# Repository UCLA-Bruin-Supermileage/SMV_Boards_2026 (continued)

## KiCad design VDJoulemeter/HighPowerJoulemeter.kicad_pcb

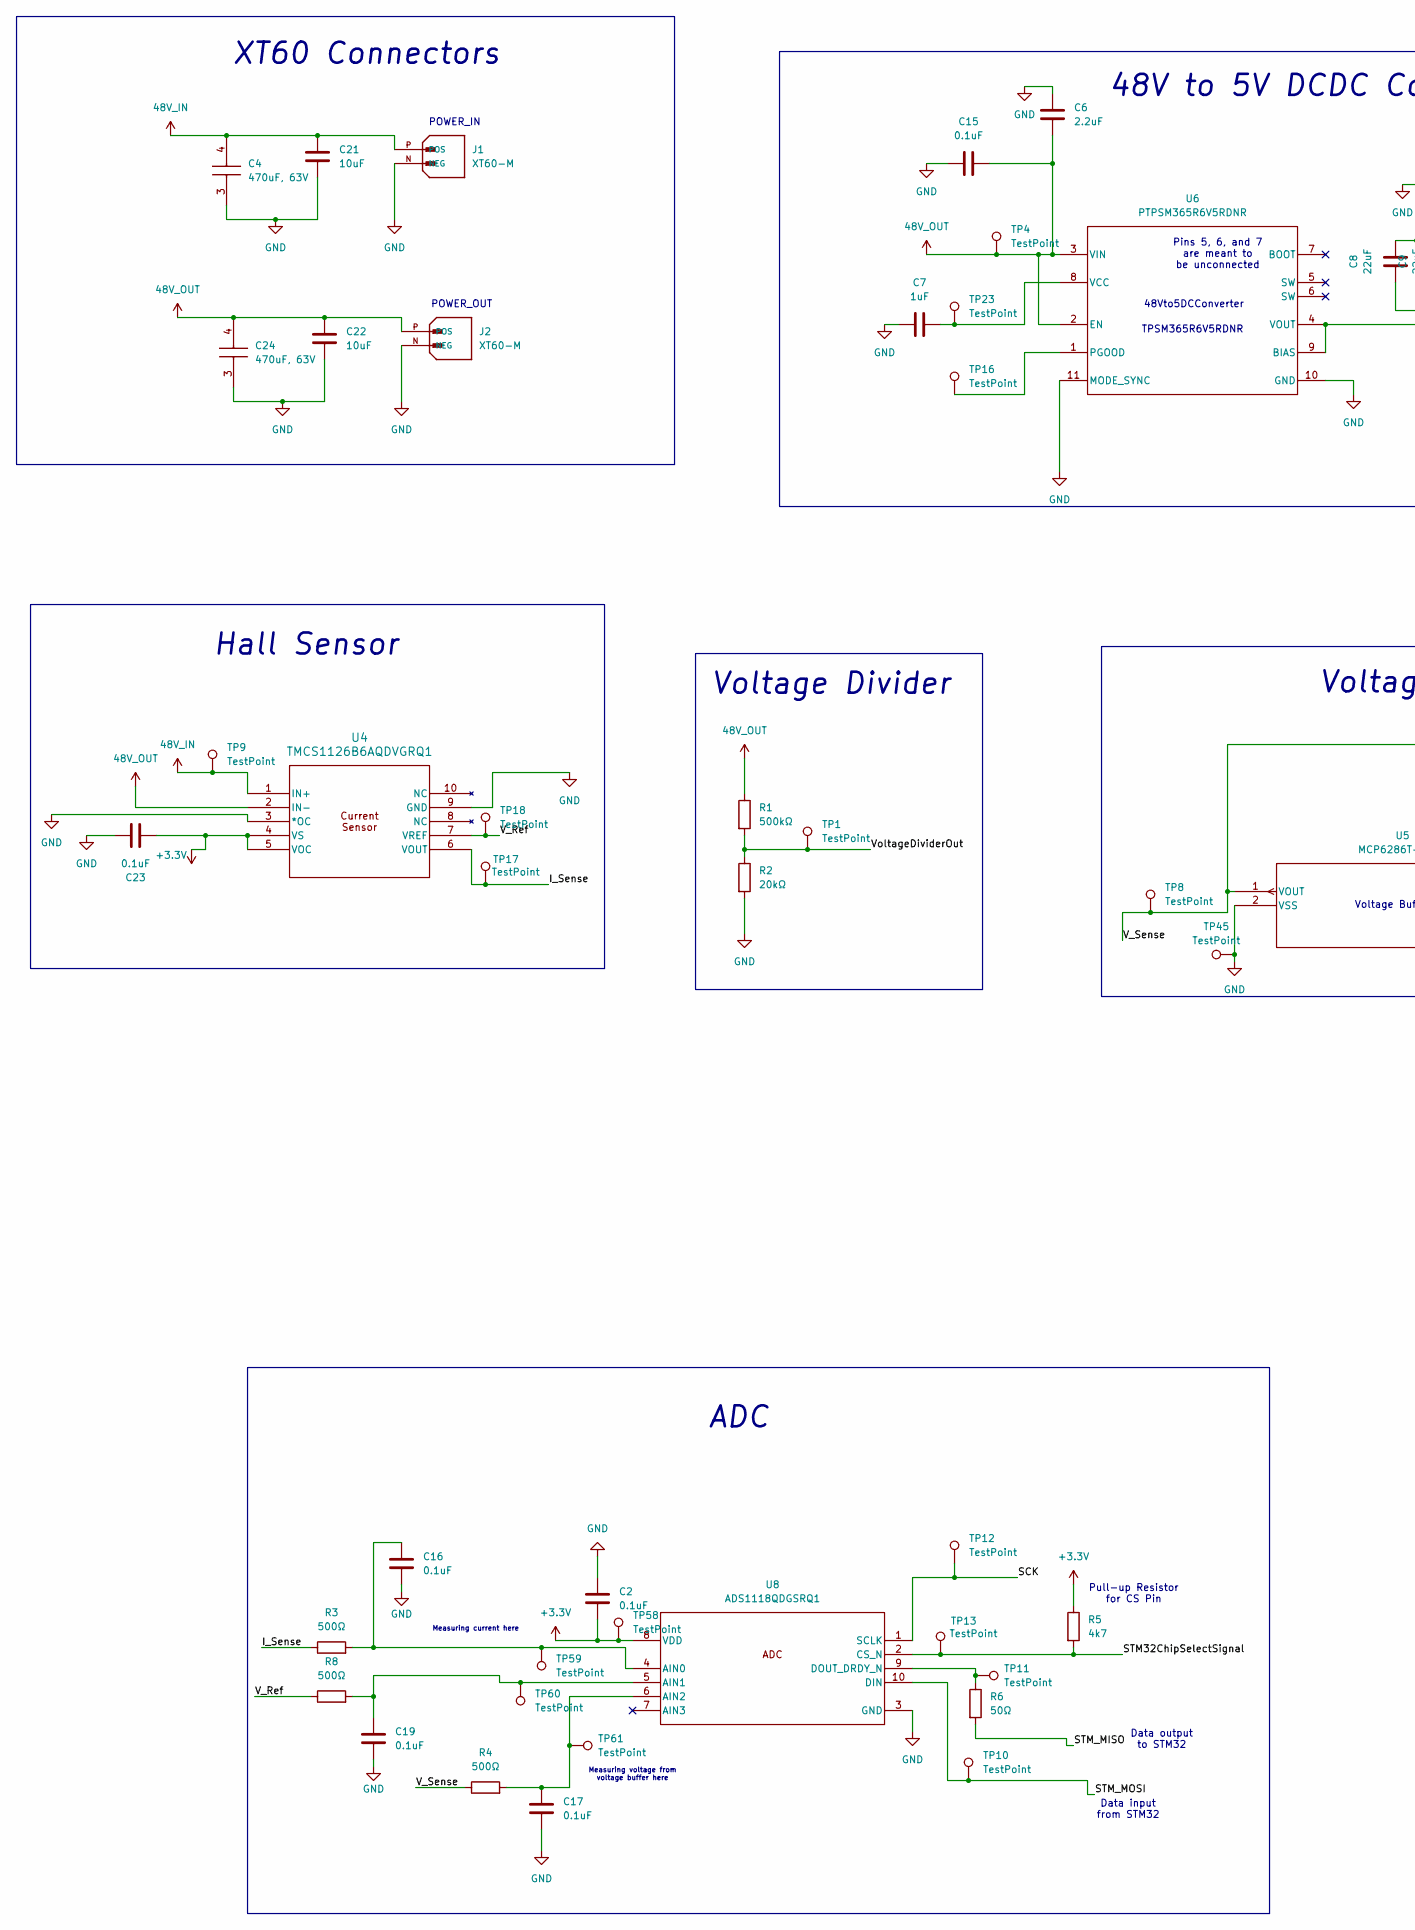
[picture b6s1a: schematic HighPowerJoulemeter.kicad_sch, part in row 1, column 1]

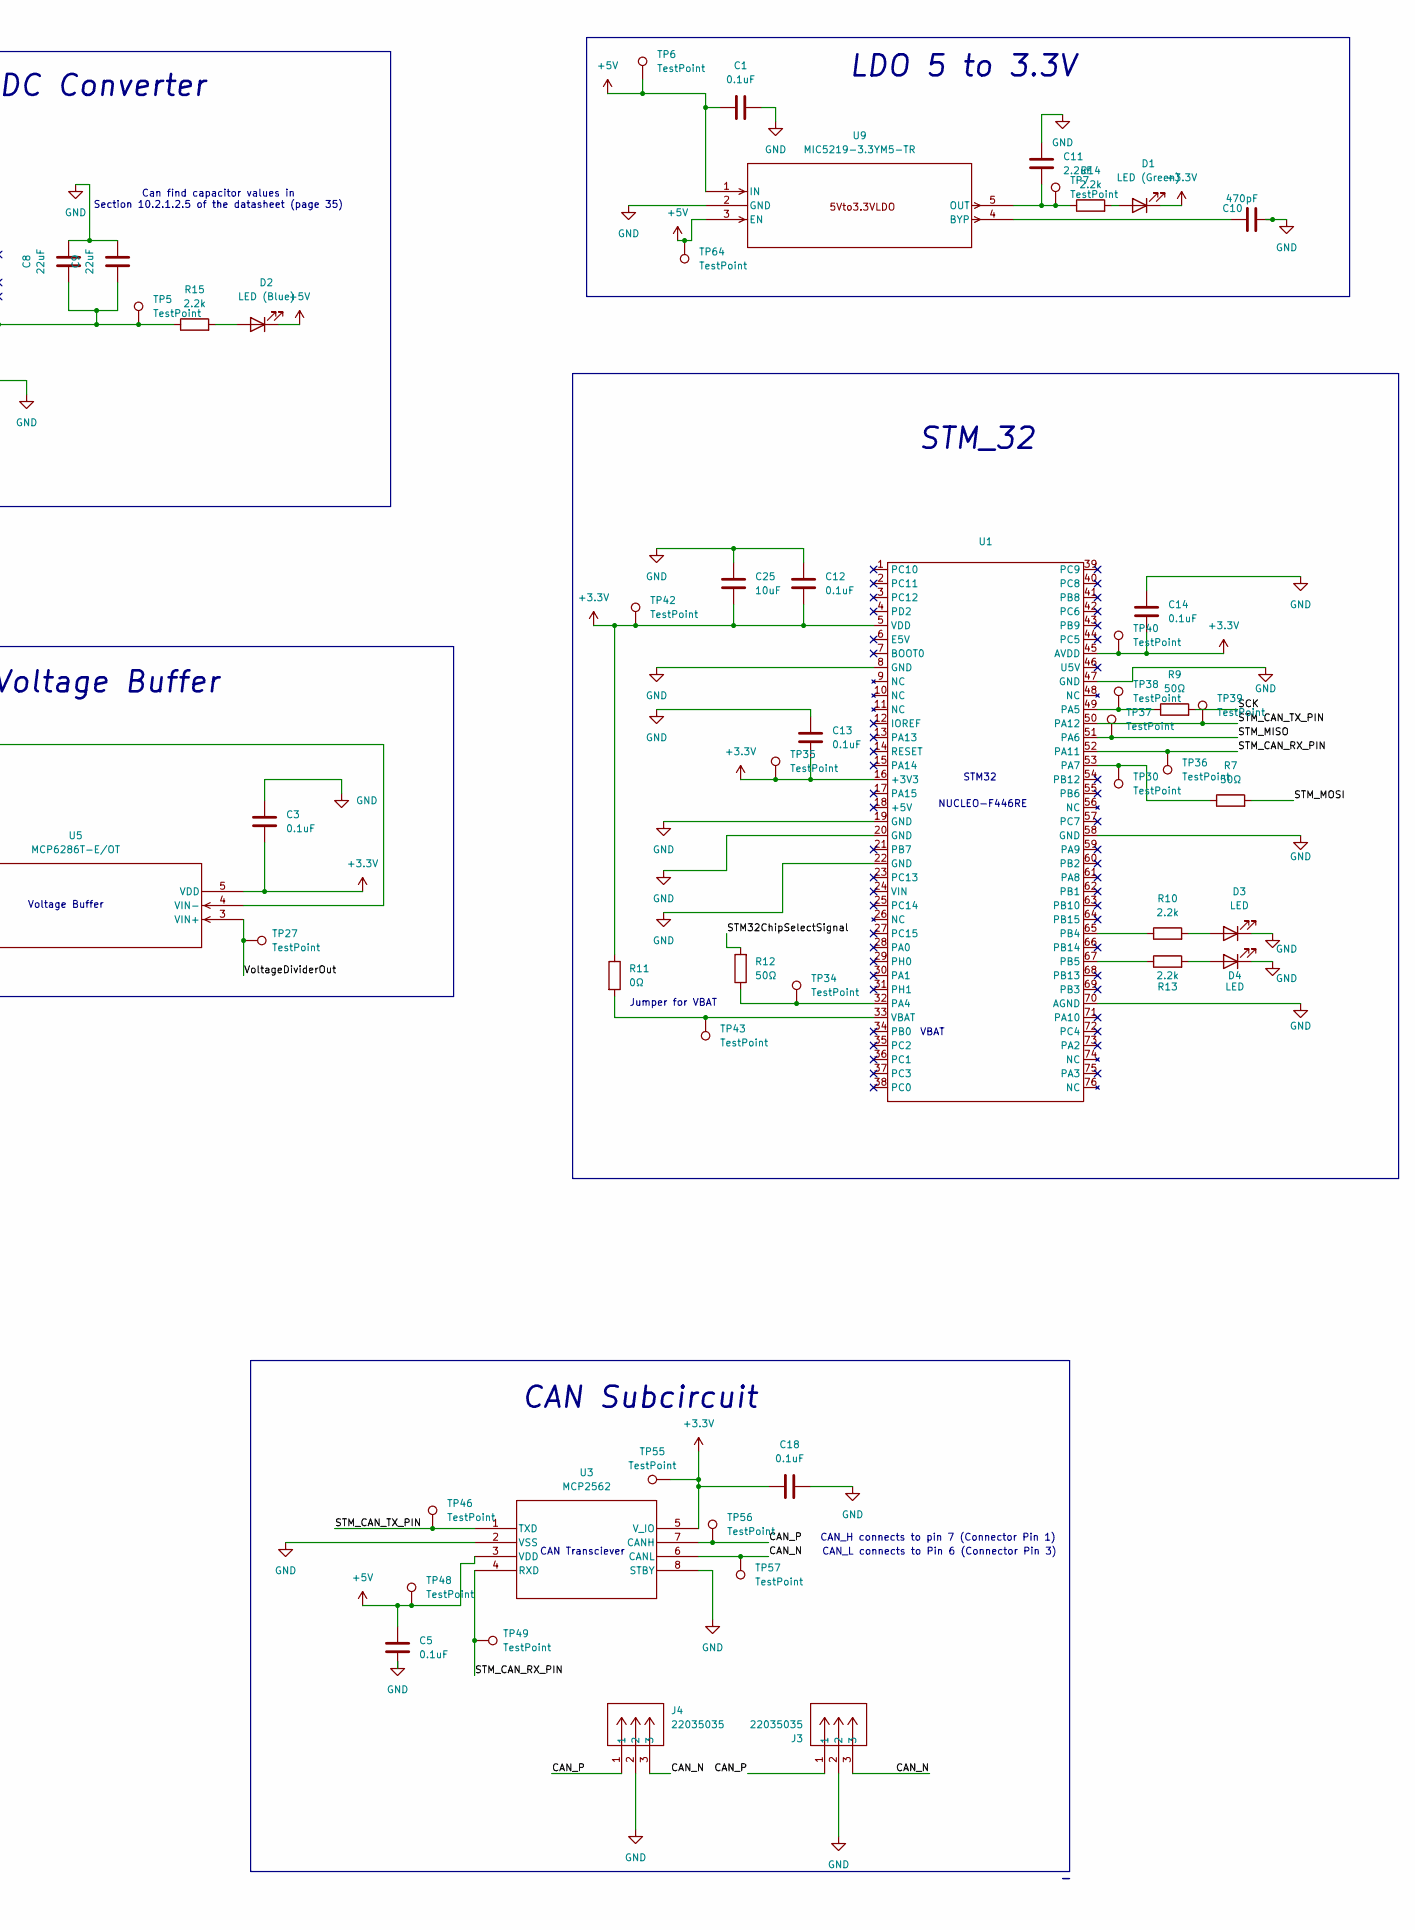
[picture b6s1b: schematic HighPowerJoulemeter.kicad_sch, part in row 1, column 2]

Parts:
C1, C2, C3, C5, C12, C13, C14, C15, C16, C17, C18, C19, C23: 0.1uF; C_0805_2012Metric_Pad1.18x1.45mm_HandSolder
C4, C24: 470uF, 63V; Big_Chunky_Cap; Manufacturer_Part_Number C0805C102K5GACTU; Mouser Part Number 80-C0805C102K5G
C6, C11: 2.2uF; C_0805_2012Metric_Pad1.18x1.45mm_HandSolder
C7: 1uF; C_0805_2012Metric_Pad1.18x1.45mm_HandSolder
C8, C9: 22uF; C_0805_2012Metric_Pad1.18x1.45mm_HandSolder
C10: 470pF; C_0805_2012Metric_Pad1.18x1.45mm_HandSolder
C21, C22, C25: 10uF; C_0805_2012Metric_Pad1.18x1.45mm_HandSolder
D1: LED (Green); R_0201_0603Metric
D2: LED (Blue); R_0201_0603Metric
D3, D4: LED; R_0201_0603Metric
J1, J2: XT60-M; AMASS_XT60-M; PARTREV V1.2
J3, J4: 22035035; 3pin_CON_22035035_MOL
R1: 500kΩ; R_0805_2012Metric_Pad1.20x1.40mm_HandSolder
R2: 20kΩ; R_0805_2012Metric_Pad1.20x1.40mm_HandSolder
R3, R4, R8: 500Ω; R_0805_2012Metric_Pad1.20x1.40mm_HandSolder
R5: 4k7; R_0805_2012Metric_Pad1.20x1.40mm_HandSolder
R6, R7, R9, R12: 50Ω; R_0805_2012Metric_Pad1.20x1.40mm_HandSolder
R10, R13, R14, R15: 2.2k; R_0805_2012Metric_Pad1.20x1.40mm_HandSolder
R11: 0Ω; R_0805_2012Metric_Pad1.20x1.40mm_HandSolder
TP1, TP4, TP5, TP6, TP7, TP8, TP9, TP10, TP11, TP12, TP13, TP16, TP17, TP18, TP23, TP27, TP30, TP34, TP35, TP36, TP37, TP38, TP39, TP40, TP42, TP43, TP45, TP46, TP48, TP49, TP55, TP56, TP57, TP58, TP59, TP60, TP61, TP64: TestPoint; TestPoint_Pad_1.0x1.0mm
U1: MODULE_NUCLEO-F446RE
U3: MCP2562; MCP2562-E_SN_SOIC8-N_MC_MCH-M
U4: TMCS1126B6AQDVGRQ1; DVG0010A-MFG
U5: MCP6286T-E/OT; SOT-23-5_MC_MCH
U6: PTPSM365R6V5RDNR; RDN0011A-MFG
U8: ADS1118QDGSRQ1; DGS0010A_N
U9: MIC5219-3.3YM5-TR; SOT-23-5_M5_MCH

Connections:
48V_IN: C4.4, C21.1, J1.P (POS), TP9.1, U4.1 (IN+)
48V_OUT: C6.2, C15.2, C22.1, C24.4, J2.P (POS), R1.1, TP4.1, U4.2 (IN-), U6.2 (EN), U6.3 (VIN); also elsewhere on the board
+3.3V: C2.2, C3.2, C12.2, C13.2, C14.2, C18.1, C23.1, C25.2, D1.1 (K), R5.1, R11.1, TP35.1, TP40.1, TP42.1, TP55.1, TP58.1, U1.5 (VDD), U1.16 (+3V3), U1.45 (AVDD), U3.5 (V_IO), U4.4 (VS), U4.5 (VOC), U5.5 (VDD), U8.8 (VDD)
+5V: C1.1, C5.1, D2.1 (K), TP6.1, TP48.1, TP64.1, U3.3 (VDD), U9.1 (IN), U9.3 (EN)
/CAN_N: J3.3, J4.3, TP57.1, U3.6 (CANL)
/CAN_P: J3.1, J4.1, TP56.1, U3.7 (CANH)
/I_Sense: R3.1, TP17.1, U4.6 (VOUT)
/SCK: R9.2, TP12.1, U8.1 (SCLK)
/STM32ChipSelectSignal: R5.2, R12.2, TP13.1, U8.2 (CS_N)
/STM_CAN_RX_PIN: TP36.1, TP49.1, U1.52 (PA11), U3.4 (RXD)
/STM_CAN_TX_PIN: TP39.1, TP46.1, U1.50 (PA12), U3.1 (TXD)
/STM_MISO: R6.2, TP37.1, U1.51 (PA6)
/STM_MOSI: R7.2, TP10.1, U8.10 (DIN)
/V_Ref: R8.1, TP18.1, U4.7 (VREF)
/V_Sense: R4.1, TP8.1, U5.1 (VOUT), U5.4 (VIN-)
/VoltageDividerOut: R1.2, R2.1, TP1.1, TP27.1, U5.3 (VIN+)
GND: C1.2, C2.1, C3.1, C4.3, C5.2, C6.1, C7.1, C8.2, C9.2, C10.2, C11.1, C12.1, C13.1, C14.1, C15.1, C16.2, C17.2, C18.2, C19.2, C21.2, C22.2, C23.2, C24.3, C25.1, D3.1 (K), D4.1 (K), J1.N (NEG), J2.N (NEG), J3.2, J4.2, R2.2, TP45.1, U1.8 (GND), U1.19 (GND), U1.20 (GND), U1.22 (GND), U1.47 (GND), U1.58 (GND), U1.70 (AGND), U3.2 (VSS), U3.8 (STBY), U4.3 (*OC), U4.9 (GND), U5.2 (VSS), U6.10 (GND), U6.11 (MODE_SYNC), U8.3 (GND), U9.2 (GND)
unnamed: D1.2 (A), R14.2
unnamed: D2.2 (A), R15.2
unnamed: D3.2 (A), R10.2
unnamed: D4.2 (A), R13.2
unnamed: R12.1, TP34.1, U1.32 (PA4)
unnamed: R9.1, TP38.1, U1.49 (PA5)
unnamed: R7.1, TP30.1, U1.53 (PA7)
unnamed: R10.1, U1.65 (PB4)
unnamed: R13.1, U1.67 (PB5)
unnamed: R11.2, TP43.1, U1.33 (VBAT)
unnamed: C8.1, C9.1, R15.1, TP5.1, U6.4 (VOUT), U6.9 (BIAS)
unnamed: TP16.1, U6.1 (PGOOD)
unnamed: C7.2, TP23.1, U6.8 (VCC)
unnamed: C16.1, R3.2, TP59.1, U8.4 (AIN0)
unnamed: C19.1, R8.2, TP60.1, U8.5 (AIN1)
unnamed: C17.1, R4.2, TP61.1, U8.6 (AIN2)
unnamed: R6.1, TP11.1, U8.9 (DOUT_DRDY_N)
unnamed: C10.1, U9.4 (BYP)
unnamed: C11.2, R14.1, TP7.1, U9.5 (OUT)

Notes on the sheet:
XT60 Connectors
Jumper for VBAT
CAN Subcircuit
CAN_H connects to pin 7 (Connector Pin 1)
Measuring current here
Pins 5, 6, and 7 are meant to be unconnected
TPSM365R6V5RDNR
Pull-up Resistor for CS Pin
Voltage Buffer
VBAT
Hall Sensor
LDO 5 to 3.3V
NUCLEO-F446RE
CAN Transciever
CAN_L connects to Pin 6 (Connector Pin 3)
Voltage Divider
48Vto5DCConverter
Measuring voltage from voltage buffer here
STM32
Data input from STM32
STM_32
48V to 5V DCDC Converter
POWER_OUT
ADC
Can find capacitor values in Section 10.2.1.2.5 of the datasheet (page 35)
POWER_IN
Data output to STM32

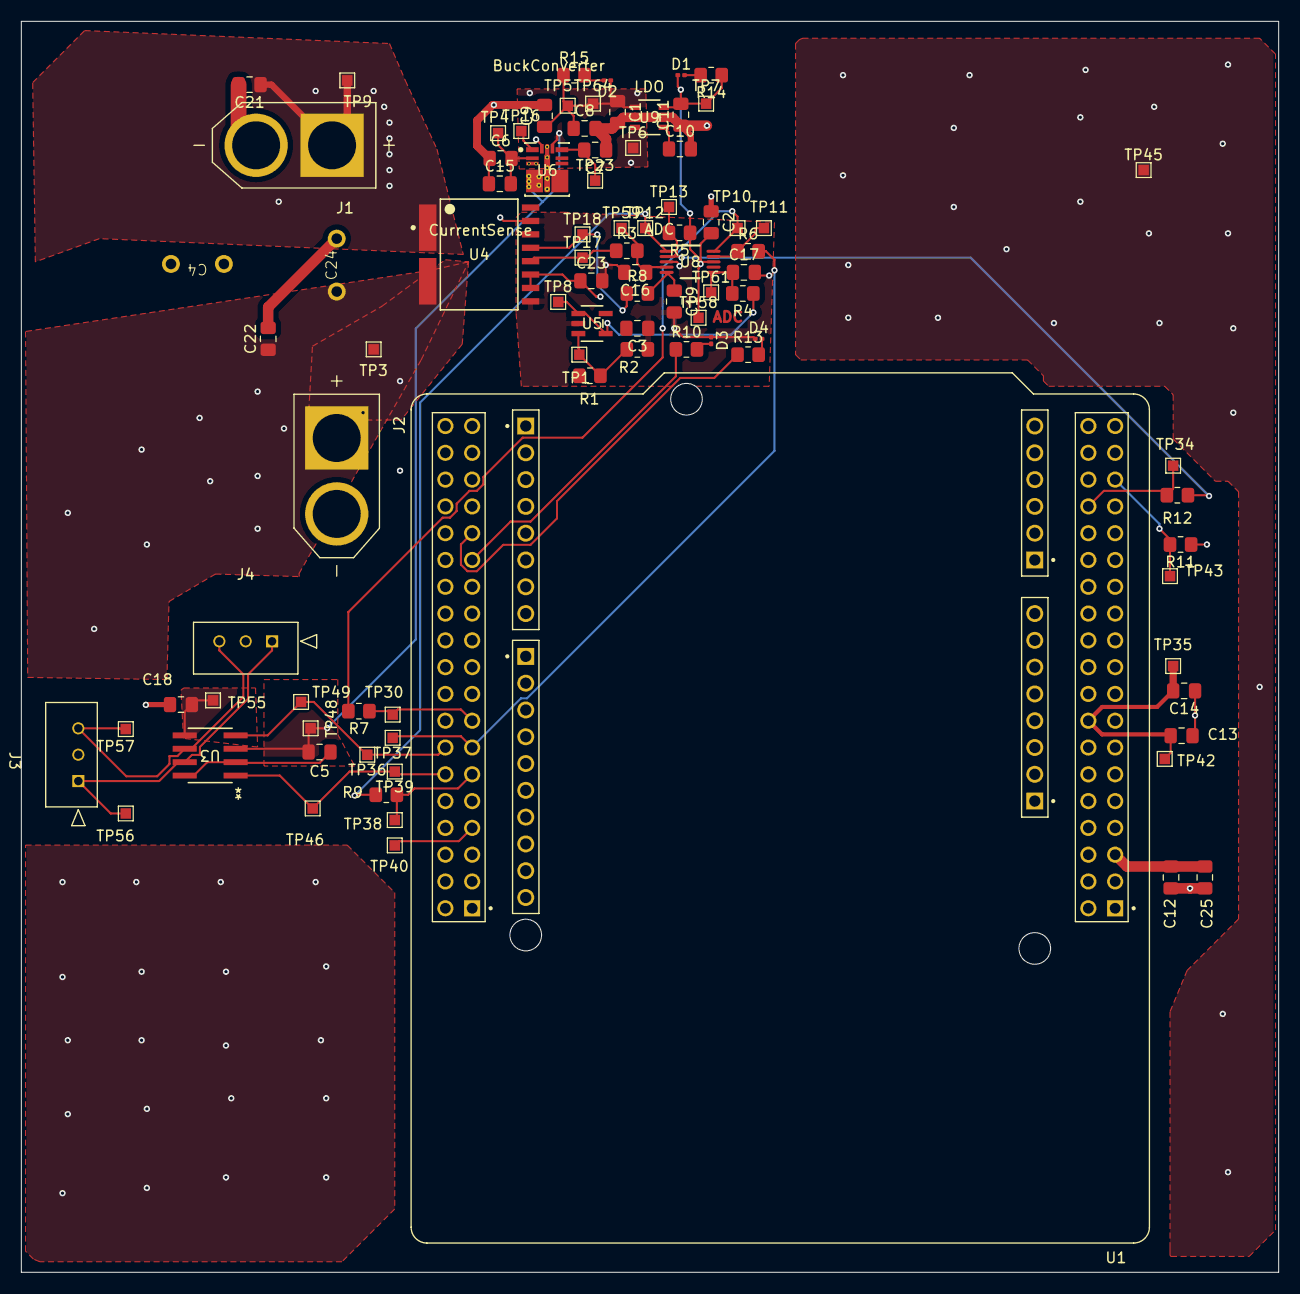
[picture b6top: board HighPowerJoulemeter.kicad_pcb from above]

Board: 4 copper layers, 119.2 x 118.6 mm, 91 parts (0 on the bottom side), 36 nets.

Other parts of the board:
TP3: TestPoint; TestPoint_Pad_1.0x1.0mm

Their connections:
48V_OUT: TP3.1; also elsewhere on the board

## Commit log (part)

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2025-07-23 Added folder
2025-07-29 Vishal's Joulemeter
2025-07-29 renamed vishal's board folder
2025-09-06 Ignore macOS .DS_Store
2025-09-07 draft1
2025-09-18 9-17-2025
2025-09-19 9-18-2025
2025-09-19 dost arrived
2025-09-19 fixes
2025-09-19 more fixes
2025-09-19 more more fixes
2025-09-19 added pdf
2025-09-19 Safwa's Joulemeter Draft 9/19/25
2025-09-19 fixes from Edwin/Patrick/Solamon feedback
2025-09-19 added RC filters for ADC inputs
2025-09-19 still need to add test pads and power symbols
2025-09-20 added symbols
2025-09-20 added some test pads
2025-09-20 Added and labeled multiple test pads
2025-09-25 crashout
2025-09-29 9-28-2025
2025-09-30 9/24 feedback stuff
2025-09-30 patrick feedback
2025-09-30 9-29-2025
2025-10-05 final draftish
2025-10-07 10-6-2025
2025-10-11 some changes from 10/11 feedbackk
2025-10-12 more changes
2025-10-12 adding safwa's backup
2025-10-12 all feedback implemented except footprints
2025-10-14 added buck footprint
2025-10-15 added a few footprints
2025-10-15 footprints
2025-10-16 added passive footprints
2025-10-16 more footprints for rest of caps
2025-10-16 added mcp footprint
2025-10-18 10-17-2025
2025-10-27 most recent schematic 10/27
2025-11-03 components
2025-11-03 all 9 components down except voltage divider lost in the jumble :'(
2025-11-03 detangling the ratsnest
2025-11-03 finished grouping
2025-11-04 Initialized Safety Board Project
2025-11-04 started safety board
2025-11-04 Created Board
2025-11-04 initial commit of project to repo
2025-11-04 markus front control board
2025-11-04 AaronWu rear control board
2025-11-04 added project folder
2025-11-04 init
2025-11-09 schematic 11/09
2025-11-09 created project in branch
2025-11-10 PCB-Layout-Draft-1
2025-11-11 added components
2025-11-11 adding my fcb schematic file
2025-11-12 layout starts
2025-11-14 added evan's ui board
2025-11-16 added can
2025-11-16 Nicholas_Tangunan_JouleMeter_Project
2025-11-16 Darell UI_Board project initial
2025-11-16 added can and power out stuff
2025-11-16 layout
2025-11-17 more layout
2025-11-17 fixed connection issues
2025-11-17 Complete Draft Layout
2025-11-18 added components
    added e-stop, DAQ thing, and hydrogen sensor(no bridge circuit yet)
2025-11-18 redo
2025-11-18 added bridge circuit
2025-11-20 PCB Complete Draft
2025-11-21 ducky
2025-11-21 edited bridge circuit
2025-11-22 edited board
2025-11-23 Schematic first draft, delete accelerometer and finish wiper circuit
2025-11-23 Accelerometer deleted, TODO: Wiper circuit
2025-11-23 Fix nested repo and add project files
2025-11-23 placed all components and connections with labels for joulemeter project
2025-11-24 Forgot 5v power to STM lol, added second 12V connector, waiting on Wiper wiring clarification
2025-11-24 Here is my draft of the UI board. I was not sure what pins to use so I choose a random few.
2025-11-24 <Schematic 1st Draft>
2025-11-24 submission for rough draft board
2025-11-24 rough draft schematic
2025-11-24 Revised Version Part 1
    Implemented changes from Google Docs and Dylan
2025-11-25 Copied last year's wiper wiring
2025-11-26 updated UI_Board_Darell_Lien
2025-11-28 UI Board
2025-11-28 starting connectors layout
2025-11-28 Add files via upload
    Phone Tshan Kyaw's UI Board
2025-11-28 please push
2025-11-29 updated ui board
2025-11-30 schematic update
2025-12-01 updated rear control board
2025-12-01 retry
2025-12-01 fixes for everything except LED layout placements and ADC shift
2025-12-02 TODO: Finish going through comments from Edwin
2025-12-02 implemented edwins feedback
2025-12-02 added new files
2025-12-02 removed unnecessary folder
2025-12-04 Built first iteration of my front control board
2025-12-05 implemented feedback #2 - need to look into differential op-amps
2025-12-11 made feedback changes, board not done
2025-12-15 Implemented feedback 1
2025-12-15 Relay
    Changed the relay to what edwin told to change it to
2025-12-16 added capacitors
2025-12-16 Work on Mac
2025-12-16 Verification Changes (No Peninsula Fixes)
2025-12-17 Updated schematic. Should have resolved all comments
2025-12-17 added decoupling capaciters
2025-12-17 Updated STM32 symbol to align with footprint
2025-12-17 draft_1
2025-12-19 Decoupling, test points, TODO: if can (voltage follower)
2025-12-19 implemented initial feedback
2025-12-20 worked on feedback
2025-12-21 Second CAN connector, grounded unused ADC pin
2025-12-23 Updated from final comments
2025-12-23 added parts respository
2025-12-23 added new nor gate
2025-12-24 schematic update, everything done but test points
2025-12-24 update nor gate and added voltage divider
2025-12-24 Added Capacitors
    Added a few decoupling capacitors. Also added a flyback diode to the mosfet.
2025-12-24 Added Capacitors v2
    Forgot somethings i think
2025-12-24 Added Capacitors v3
    Added the proper decoupling capacitors i think. I still dont rly understand what they are :(
2025-12-25 test points
2025-12-26 this is my updated version of the board
2025-12-27 Joule Meter Final
    -Removed Pinnulas
    -Added specific capacitor links for capacitors with a 48V across.
2025-12-27 first draft PCB
2025-12-27 Joule Meter Final
    Added a second test pad for the ground. The idea is that we can connect a wire across these two to make a test loop.
2025-12-28 added LED for testing
2025-12-29 Finished schematic, waiting on jumper clarification, starting layout
2025-12-29 Complted schematic design
2025-12-30 just pushing, idk why it says its not up to date
2025-12-30 added footprints
2025-12-30 PCB first draft
2025-12-31 fixed vias, made power traces wider
2026-01-01 updated PCB
2026-01-01 implemented feedback
2026-01-02 feedback work
2026-01-03 test points added schematic done
2026-01-04 made board smaller, cleaned up silkscreen
2026-01-05 feedback
2026-01-05 cleaned some stuff up
2026-01-05 minor courtyard moves
2026-01-05 fixing silkscreen a bit
2026-01-05 rerouted differential traced for CAN
2026-01-06 started layout, backing up early bc laptop broke
2026-01-06 Create empty branch diverging from main
2026-01-06 Add project title and description to README
2026-01-06 Create UIBoard PHONE&DONLD
2026-01-06 updated schematic 1/5
2026-01-06 idk why the versions back tracked 3 weeks
2026-01-06 feedback updates
2026-01-06 changed SPLIT pin to 5V
2026-01-06 Fixed nets for STM32 and 7 Segment Display
2026-01-06 added capacitor values
2026-01-07 replaced relay
2026-01-07 Fixed STM32 footprint
2026-01-07 Changed sm things
2026-01-07 fixed missing ratsnests, updating from MSI laptop
2026-01-07 placing subsystems on layout
2026-01-07 TODO: finish layout lol
2026-01-07 schematic done
2026-01-08 edits
2026-01-08 updated schematic 1/8
2026-01-08 draft 2
2026-01-09 sorry edwin here is the board
2026-01-09 minor silkscreen edits
2026-01-10 more silkscreen edits
2026-01-10 Implemented feedbacks from 1/5
2026-01-10 Updated layout UIBoard PHONE&DONALD
2026-01-10 Added layout feedback
2026-01-11 updated schematic
2026-01-11 updated jm schematic
2026-01-12 some tweaks?
2026-01-13 Feedback Implementation
    - Labeled Capacitors + Resistors
    - Relabeled Nor Gate Inputs
    - Added additional power symbols
    - Added Pull-Up Resistors for E-Stops
    - Changed Relay Output to be based on MOSFET being on/off rather than out of relay(idk if this is correct)
2026-01-13 placements should be good? 12V corner, 5v corner, analog side, CAN bottom. Get confirmation and start tracing
2026-01-13 Create UIBoard_PHONE&DONALD
    Updated feedback for layout
2026-01-13 Updated layout based on new feedback
2026-01-14 changed the inductor footprint
2026-01-14 added footprints and other stuff
2026-01-14 1/13 Update
2026-01-14 layout confirmed, just need to draw traces and pour
2026-01-14 Inductor Update
2026-01-14 ready to order
2026-01-14 Final Board
2026-01-15 pcb layout
2026-01-16 12v pours done, finalize placements of some subsystems and then run traces, also place all my vias
2026-01-17 vias placed?
2026-01-17 schematic and pcb layout
2026-01-17 Create UI_Board_PHONE&DONALD
    Update on layout before review
2026-01-17 Updated layout before review
2026-01-17 updated schematic based on 2nd round feedback
2026-01-18 Organized Layout
    Put corresponding components next to each other
2026-01-18 finished changes for 2nd feedback round
2026-01-18 Final Board Draft (I think)
2026-01-18 connection points
2026-01-18 added test points
2026-01-18 Layout Changes
2026-01-18 r values changes
2026-01-19 added connector
2026-01-19 repush
2026-01-19 update placement
2026-01-19 gurt
2026-01-19 added comparator
2026-01-19 Done w first draft! waiting for feedback
2026-01-19 fixed some minor things, unconnected vias and test points
2026-01-19 Here is my latest draft of the layout. Please review the connections for the multiplexer. I was looking at the datasheet and found that it was wired incorrectly.
2026-01-19 Added Traces
    Traces for relay, voltage regulator, nor gate, e-stops
2026-01-20 Traces Cont...
    Changed Potentiometer footprint
    Routed Hydrogen comp comparators
    Did a bit of the CAN connections but its incomplete
    Dont forget to add filled zone at the end
2026-01-20 finish layout
2026-01-20 Two-Layered board based on feedback
2026-01-21 changed a few resistor values
2026-01-21 changed led footprint
2026-01-21 hall sensor fix
2026-01-22 drc fixes
2026-01-22 LEDs added, mosfet ground polygons, Ground plane, slight rerouting
2026-01-22 pcb push
2026-01-22 PCB Changes
    Reduced Layers 4 -> 2
    Retraced as needed
2026-01-22 Create UIBoard PHONE&DONALD
    End-phase board feedback
2026-01-22 made a few layout changes
2026-01-23 Made edits before Edwin made his edits: replaced CANTran footprint, rerouted jumper for RX/TX, added LED for 3v3
2026-01-23 draft3
2026-01-24 Small tuning for UI Board
2026-01-24 Small tuning to UI Board
2026-01-24 PCB Feedback Implementation
2026-01-25 pcb feedback
2026-01-25 made a few minor changes to layout
2026-01-25 readded minor changes
2026-01-25 traces width
2026-01-25 Layout Feedback Updates
2026-01-28 draft 4
2026-01-28 updated layout
2026-02-01 changes to sch
2026-02-01 hsensor schematic changes
2026-02-01 sch to pcb
2026-02-02 joulemeter layout - needs traces . also i hope this doesnt break anything teehee
2026-02-03 Create UIBoard PHONE&DONALD
    Few small tweaks to layout and schematic
2026-02-03 Few small tweaks to layout and schematic
2026-02-04 schematic changes
2026-02-05 sch update
2026-02-06 Layout connections
    mostly done, final connections at the inverter and size might be reducable
2026-02-08 sch changes
2026-02-09 3 relay pain
2026-02-09 component placement
2026-02-09 Relay layout
2026-02-10 hydrogen
2026-02-10 placement changes
2026-02-11 comp placement
2026-02-11 PCB Adjustments
2026-02-12 PCB Changes after Dylan/Patrick idk tbh
2026-02-13 sch 3v3 changes
2026-02-13 can routing
2026-02-13 PCB Routing
2026-02-14 routing
2026-02-14 routing updated
2026-02-14 width changes
2026-02-14 board update
2026-02-16 Schematic Changes(Contactor system)
2026-02-16 estop changes
2026-02-16 nah it is joover
2026-02-17 bruh
2026-02-18 removed relays
2026-02-18 added relays
2026-02-18 sch change
2026-02-19 grouped components together
2026-02-19 pcb placements
2026-02-19 layout update
2026-02-21 changed ldo
2026-02-22 niche
2026-02-23 footprint update
2026-02-23 holy
2026-02-24 Power thingy revamp + Silkscreen Updates
2026-02-25 layout fixes
2026-02-25 opps
2026-02-27 updated silkscreen
2026-02-28 LED Changes
    -Fixed LED so that Relay U5 wouldn't always be on
2026-02-28 small changes to the pcb
2026-03-01 updated led positioning
2026-03-01 connected leds to gate
2026-03-02 led changes
2026-03-02 switch pins for can tx and rx
2026-03-02 feedback from soloman
    made routing further from pads, swapped canl and canh, and added more stitching
2026-03-04 changed capacitor footprint and fixed a few drc errors
2026-03-04 changed diode footprint
2026-04-09 can polarity
2026-04-28 Added Thermal Reliefs
2026-05-01 added a polygon
2026-05-01 Added more test points
2026-05-03 Create UI BOARD PHONE&DONALD
2026-05-03 Added LEDs
2026-05-03 added two new caps next to ferrite bead
2026-05-03 added a few more vias
2026-05-03 Final Touch Up, Silk Screen
2026-05-03 changed 20k potentometer footprint
2026-05-03 finished
2026-05-03 finished, need fix silkscreen
2026-05-04 Done! Serg Ed have looked at relay circ
2026-05-04 Done! Ed and Serg checked relay
